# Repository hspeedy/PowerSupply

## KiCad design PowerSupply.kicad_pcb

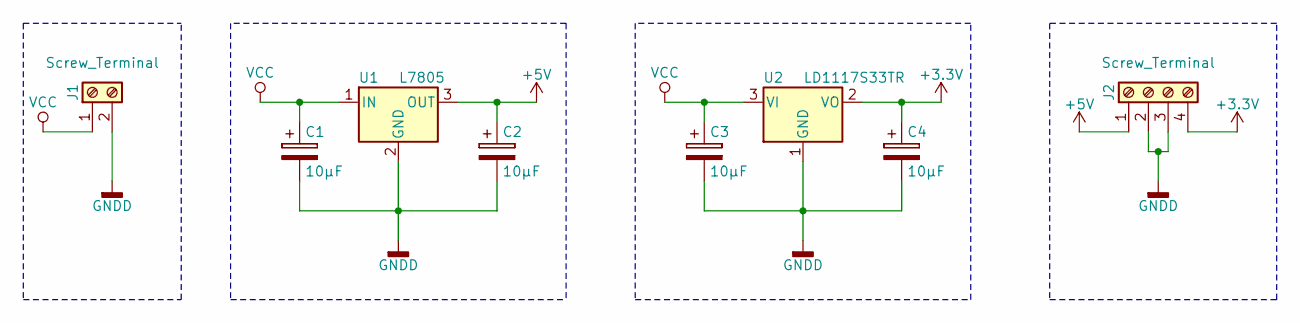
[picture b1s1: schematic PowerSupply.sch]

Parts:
C1, C2, C3, C4: 10µF; CP_Radial_D5.0mm_P2.50mm
J1: Screw_Terminal; mstba_2,5%2f2-g-5,08
J2: Screw_Terminal; mstba_2,5%2f4-g-5,08
U1: L7805; TO-220-3_Horizontal
U2: LD1117S33TR; TO-220-3_Horizontal

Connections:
+3V3: C4.1, J2.4, U2.2 (VO)
+5V: C2.1, J2.1, U1.3 (OUT)
GNDD: C1.2, C2.2, C3.2, C4.2, J1.2, J2.2, J2.3, U1.2 (GND), U2.1 (GND)
VCC: C1.1, C3.1, J1.1, U1.1 (IN), U2.3 (VI)

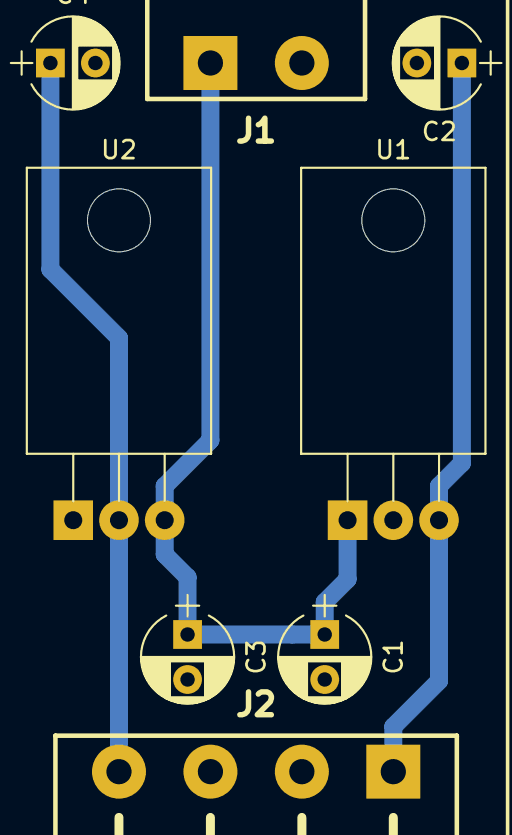
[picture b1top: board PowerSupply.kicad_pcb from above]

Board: 2 copper layers, 8 parts (0 on the bottom side), 4 nets.

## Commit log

2018-01-21 Added printable parts
2018-01-21 F Silk
2018-01-21 added pdf
